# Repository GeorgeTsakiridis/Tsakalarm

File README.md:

# Tsakalarm
Tsakalarm is an open source project which includes the construction of a bedside table alarm clock, the software it runs as well as an Android app for easily configuring it

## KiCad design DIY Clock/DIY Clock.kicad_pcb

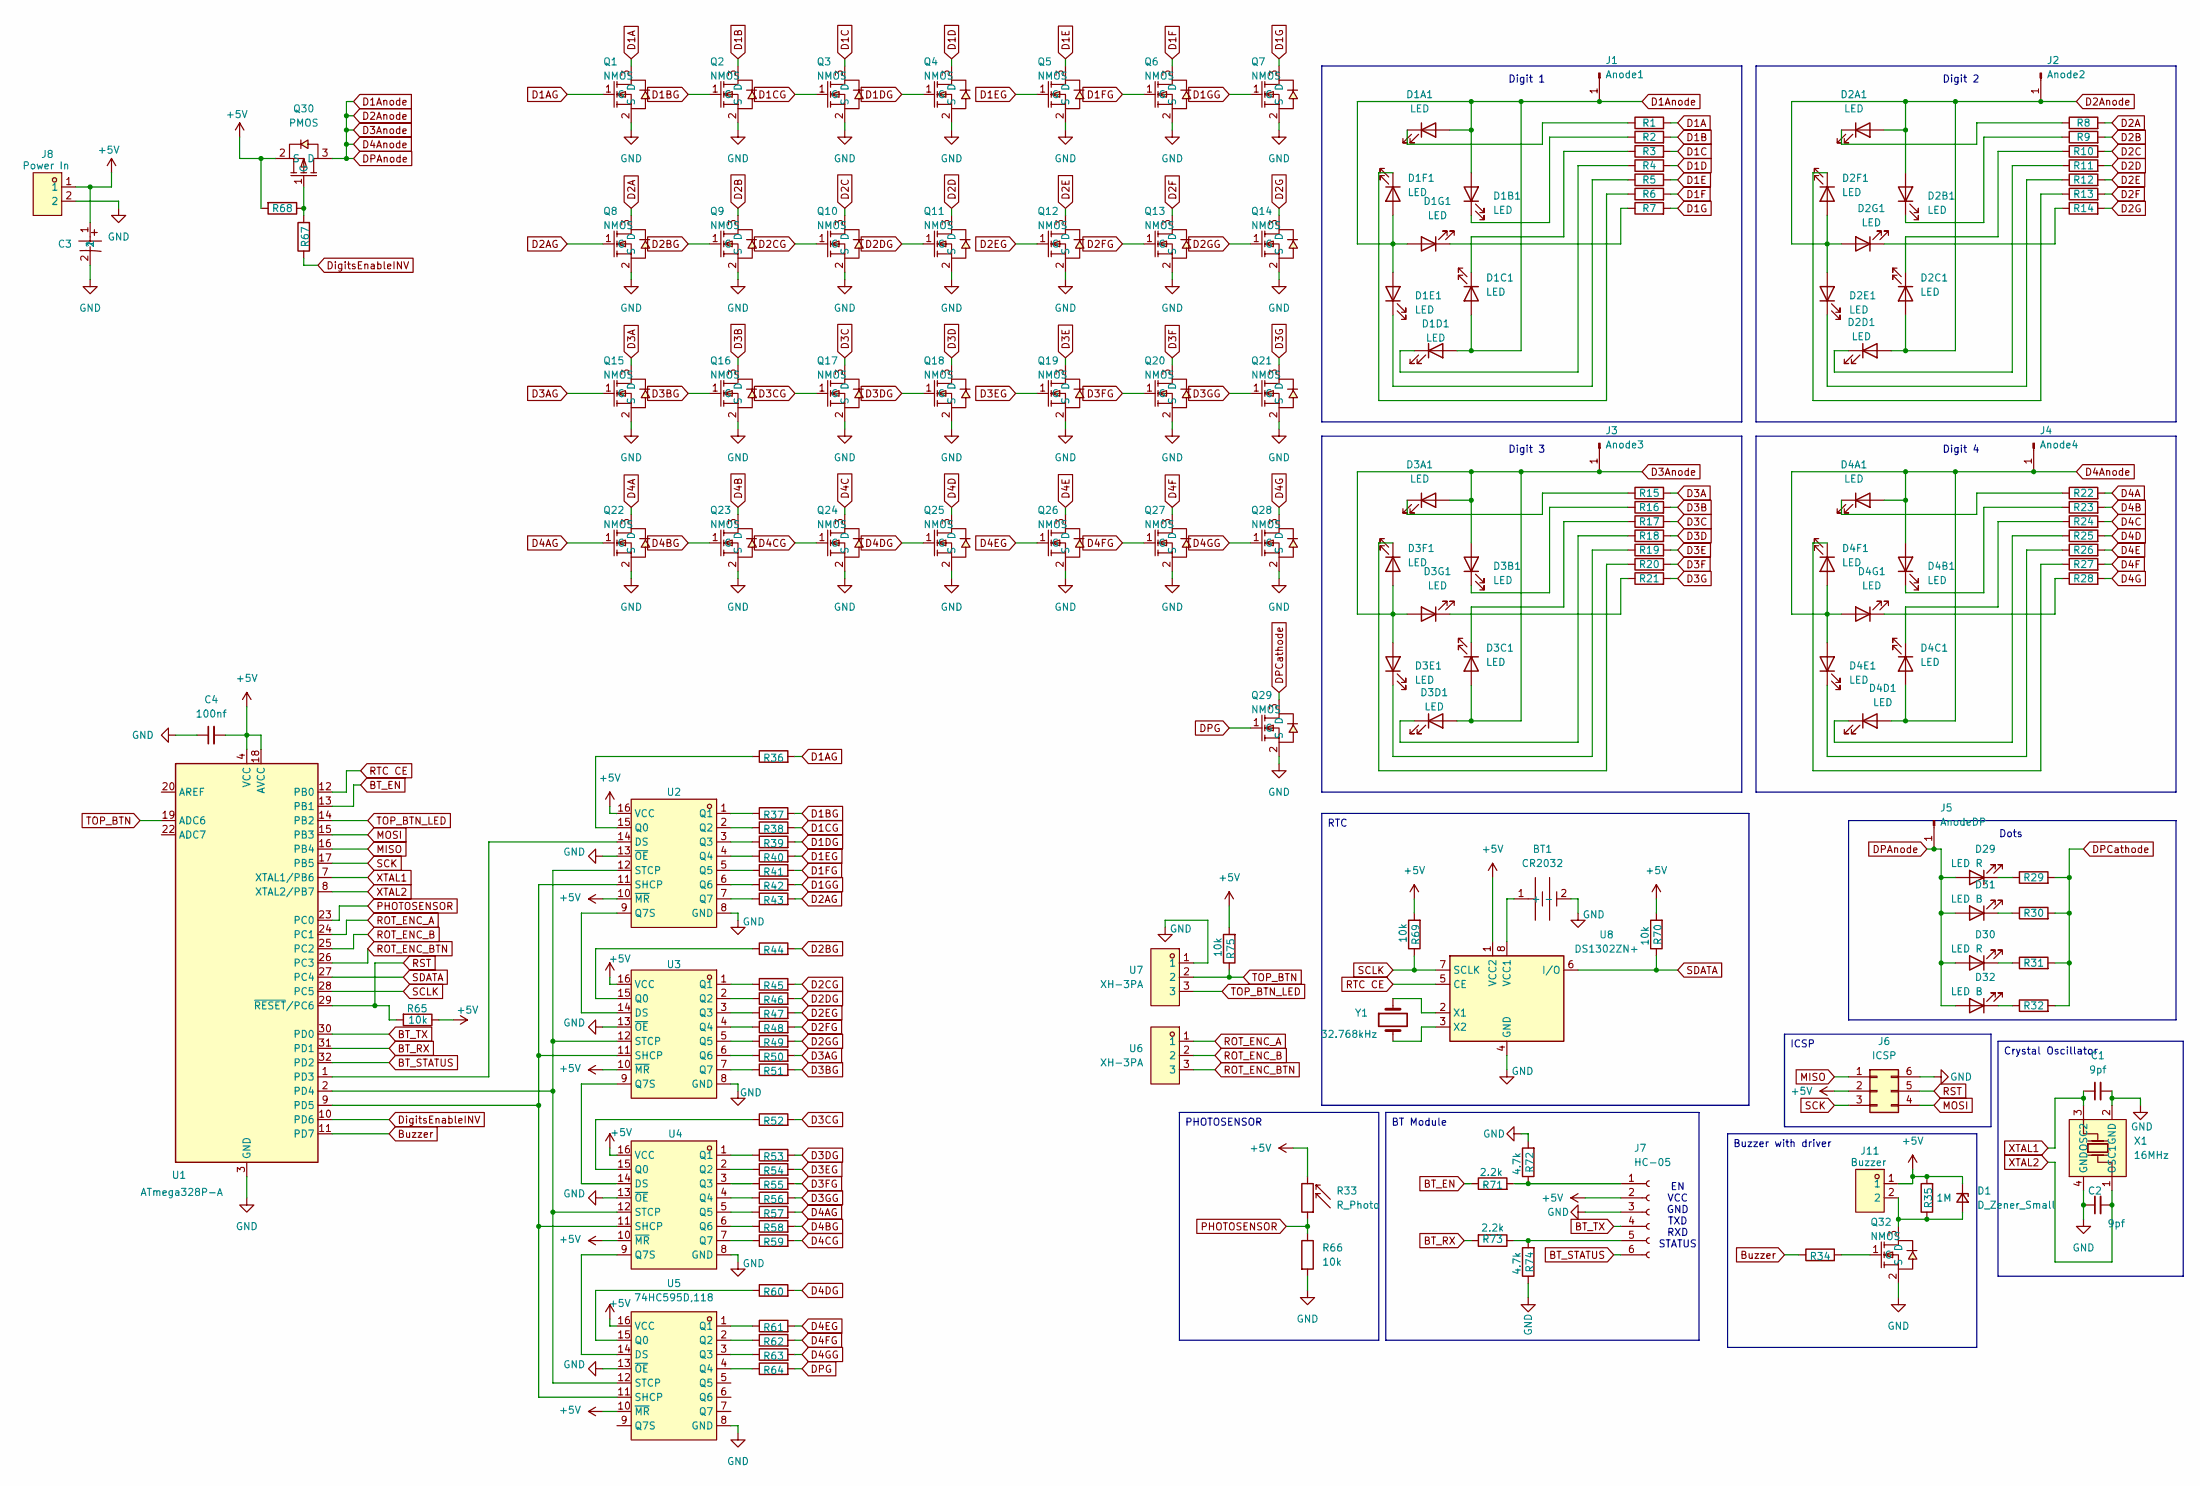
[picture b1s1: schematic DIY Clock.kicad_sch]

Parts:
BT1: CR2032; BAT-TH_120591-1; LCSC Part C575181
C1, C2: 9pf; C_0805_2012Metric_Pad1.18x1.45mm_HandSolder
C3: 35PX1000MEFC10X20; CAP-TH_BD10.0-P5.00-D1.0-FD; LCSC Part C136014
C4: 100nf; C_0805_2012Metric_Pad1.18x1.45mm_HandSolder
D1: D_Zener_Small; LL-34_L3.5-W1.5-RD
D1A1, D1B1, D1C1, D1D1, D1E1, D1F1, D1G1, D2A1, D2B1, D2C1, D2D1, D2E1, D2F1, D2G1, D3A1, D3B1, D3C1, D3D1, D3E1, D3F1, D3G1, D4A1, D4B1, D4C1, D4D1, D4E1, D4F1, D4G1: LED; PinHeader_1x01_P2.54mm_Vertical
D29, D30: LED R; PinHeader_1x01_P2.54mm_Vertical
D31, D32: LED B; PinHeader_1x01_P2.54mm_Vertical
J1: Anode1; PinHeader_1x01_P2.54mm_Vertical
J2: Anode2; PinHeader_1x01_P2.54mm_Vertical
J3: Anode3; PinHeader_1x01_P2.54mm_Vertical
J4: Anode4; PinHeader_1x01_P2.54mm_Vertical
J5: AnodeDP; PinHeader_1x01_P2.54mm_Vertical
J6: ICSP; PinHeader_2x03_P2.54mm_Vertical
J7: HC-05; PinHeader_1x06_P2.54mm_Vertical
J8: Power In; CONN-TH_XH-2A; LCSC Part C5258883
J11: Buzzer; PinHeader_1x02_P2.54mm_Vertical; LCSC Part C5258883
Q1, Q2, Q3, Q4, Q5, Q6, Q7, Q8, Q9, Q10, Q11, Q12, Q13, Q14, Q15, Q16, Q17, Q18, Q19, Q20, Q21, Q22, Q23, Q24, Q25, Q26, Q27, Q28, Q29, Q32: NMOS; SOT-23-3_L2.9-W1.3-P1.90-LS2.4-BR; LCSC Part C347475
Q30: PMOS; SOT-23_L2.9-W1.3-P1.90-LS2.4-BR; LCSC Part C347476
R1, R2, R3, R4, R5, R6, R7, R8, R9, R10, R11, R12, R13, R14, R15, R16, R17, R18, R19, R20, R21, R22, R23, R24, R25, R26, R27, R28, R29, R30, R31, R32: R; R_0805_2012Metric_Pad1.20x1.40mm_HandSolder
R33: R_Photo; PinHeader_1x02_P2.54mm_Vertical
R34, R36, R37, R38, R39, R40, R41, R42, R43, R44, R45, R46, R47, R48, R49, R50, R51, R52, R53, R54, R55, R56, R57, R58, R59, R60, R61, R62, R63, R64, R67: 1k; R_0805_2012Metric_Pad1.20x1.40mm_HandSolder
R35: 1M; R_0805_2012Metric_Pad1.20x1.40mm_HandSolder
R65, R66, R68, R69, R70, R75: 10k; R_0805_2012Metric_Pad1.20x1.40mm_HandSolder
R71, R73: 2.2k; R_0805_2012Metric_Pad1.20x1.40mm_HandSolder
R72, R74: 4.7k; R_0805_2012Metric_Pad1.20x1.40mm_HandSolder
U1: ATmega328P-A; TQFP-32_7x7mm_P0.8mm
U2, U3, U4, U5: 74HC595D,118; SOIC-16_L9.9-W3.9-P1.27-LS6.0-BL; LCSC Part C5947
U6, U7: XH-3PA; CONN-TH_3P-P2.50_ZHOURI_XH-3PA; LCSC Part C5258884
U8: DS1302ZN+; SOIC-8_3.9x4.9mm_P1.27mm
X1: 16MHz; CRYSTAL-SMD_4P-L3.2-W2.5-BL; LCSC Part C390767
Y1: 32.768kHz; Crystal_DS26_D2.0mm_L6.0mm_Horizontal

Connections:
+5V: C3.1, C4.2, D1.1 (K), J6.2, J7.2, J8.1, J11.1, Q30.2 (S), R33.2, R35.2, R65.1, R68.2, R69.2, R70.2, R75.2, U1.4 (VCC), U1.6 (VCC), U1.18 (AVCC), U2.10 (~MR), U2.16 (VCC), U3.10 (~MR), U3.16 (VCC), U4.10 (~MR), U4.16 (VCC), U5.10 (~MR), U5.16 (VCC), U8.1 (VCC2)
BT_EN: R71.1, U1.13 (PB1)
BT_RX: R73.2, U1.31 (PD1)
BT_STATUS: J7.6, U1.32 (PD2)
BT_TX: J7.4, U1.30 (PD0)
Buzzer: R34.1, U1.11 (PD7)
D1A: Q1.3 (D), R1.2
D1AG: Q1.1 (G), R36.2
D1Anode: D1A1.2 (A), D1B1.2 (A), D1C1.2 (A), D1D1.2 (A), D1E1.2 (A), D1F1.2 (A), D1G1.2 (A), D2A1.2 (A), D2B1.2 (A), D2C1.2 (A), D2D1.2 (A), D2E1.2 (A), D2F1.2 (A), D2G1.2 (A), D3A1.2 (A), D3B1.2 (A), D3C1.2 (A), D3D1.2 (A), D3E1.2 (A), D3F1.2 (A), D3G1.2 (A), D4A1.2 (A), D4B1.2 (A), D4C1.2 (A), D4D1.2 (A), D4E1.2 (A), D4F1.2 (A), D4G1.2 (A), D29.2 (A), D30.2 (A), D31.2 (A), D32.2 (A), J1.1, J2.1, J3.1, J4.1, J5.1, Q30.3 (D)
D1B: Q2.3 (D), R2.2
D1BG: Q2.1 (G), R37.2
D1C: Q3.3 (D), R3.2
D1CG: Q3.1 (G), R38.2
D1D: Q4.3 (D), R4.2
D1DG: Q4.1 (G), R39.2
D1E: Q5.3 (D), R5.2
D1EG: Q5.1 (G), R40.2
D1F: Q6.3 (D), R6.2
D1FG: Q6.1 (G), R41.2
D1G: Q7.3 (D), R7.2
D1GG: Q7.1 (G), R42.2
D2A: Q8.3 (D), R8.2
D2AG: Q8.1 (G), R43.2
D2B: Q9.3 (D), R9.2
D2BG: Q9.1 (G), R44.2
D2C: Q10.3 (D), R10.2
D2CG: Q10.1 (G), R45.2
D2D: Q11.3 (D), R11.2
D2DG: Q11.1 (G), R46.2
D2E: Q12.3 (D), R12.2
D2EG: Q12.1 (G), R47.2
D2F: Q13.3 (D), R13.2
D2FG: Q13.1 (G), R48.2
D2G: Q14.3 (D), R14.2
D2GG: Q14.1 (G), R49.2
D3A: Q15.3 (D), R15.2
D3AG: Q15.1 (G), R50.2
D3B: Q16.3 (D), R16.2
D3BG: Q16.1 (G), R51.2
D3C: Q17.3 (D), R17.2
D3CG: Q17.1 (G), R52.2
D3D: Q18.3 (D), R18.2
D3DG: Q18.1 (G), R53.2
D3E: Q19.3 (D), R19.2
D3EG: Q19.1 (G), R54.2
D3F: Q20.3 (D), R20.2
D3FG: Q20.1 (G), R55.2
D3G: Q21.3 (D), R21.2
D3GG: Q21.1 (G), R56.2
D4A: Q22.3 (D), R22.2
D4AG: Q22.1 (G), R57.2
D4B: Q23.3 (D), R23.2
D4BG: Q23.1 (G), R58.2
D4C: Q24.3 (D), R24.2
D4CG: Q24.1 (G), R59.2
D4D: Q25.3 (D), R25.2
D4DG: Q25.1 (G), R60.2
D4E: Q26.3 (D), R26.2
D4EG: Q26.1 (G), R61.2
D4F: Q27.3 (D), R27.2
D4FG: Q27.1 (G), R62.2
D4G: Q28.3 (D), R28.2
D4GG: Q28.1 (G), R63.2
DPCathode: Q29.3 (D), R29.2, R30.2, R31.2, R32.2
DPG: Q29.1 (G), R64.2
DigitsEnableINV: R67.1, U1.10 (PD6)
GND: BT1.2 (-), C1.2, C2.1, C3.2, C4.1, J6.6, J7.3, J8.2, Q1.2 (S), Q2.2 (S), Q3.2 (S), Q4.2 (S), Q5.2 (S), Q6.2 (S), Q7.2 (S), Q8.2 (S), Q9.2 (S), Q10.2 (S), Q11.2 (S), Q12.2 (S), Q13.2 (S), Q14.2 (S), Q15.2 (S), Q16.2 (S), Q17.2 (S), Q18.2 (S), Q19.2 (S), Q20.2 (S), Q21.2 (S), Q22.2 (S), Q23.2 (S), Q24.2 (S), Q25.2 (S), Q26.2 (S), Q27.2 (S), Q28.2 (S), Q29.2 (S), Q32.2 (S), R66.2, R72.2, R74.1, U1.3 (GND), U1.5 (GND), U1.21 (GND), U2.8 (GND), U2.13 (~OE), U3.8 (GND), U3.13 (~OE), U4.8 (GND), U4.13 (~OE), U5.8 (GND), U5.13 (~OE), U7.1, U8.4 (GND), X1.2 (GND), X1.4 (GND)
MISO: J6.1, U1.16 (PB4)
MOSI: J6.4, U1.15 (PB3)
unnamed: BT1.1 (+), U8.8 (VCC1)
unnamed: D1.2 (A), J11.2, Q32.3 (D), R35.1
unnamed: D1A1.1 (K), R1.1
unnamed: D1B1.1 (K), R2.1
unnamed: D1C1.1 (K), R3.1
unnamed: D1D1.1 (K), R4.1
unnamed: D1E1.1 (K), R5.1
unnamed: D1F1.1 (K), R6.1
unnamed: D1G1.1 (K), R7.1
unnamed: D2A1.1 (K), R8.1
unnamed: D2B1.1 (K), R9.1
unnamed: D2C1.1 (K), R10.1
unnamed: D2D1.1 (K), R11.1
unnamed: D2E1.1 (K), R12.1
unnamed: D2F1.1 (K), R13.1
unnamed: D2G1.1 (K), R14.1
unnamed: D3A1.1 (K), R15.1
unnamed: D3B1.1 (K), R16.1
unnamed: D3C1.1 (K), R17.1
unnamed: D3D1.1 (K), R18.1
unnamed: D3E1.1 (K), R19.1
unnamed: D3F1.1 (K), R20.1
unnamed: D3G1.1 (K), R21.1
unnamed: D4A1.1 (K), R22.1
unnamed: D4B1.1 (K), R23.1
unnamed: D4C1.1 (K), R24.1
unnamed: D4D1.1 (K), R25.1
unnamed: D4E1.1 (K), R26.1
unnamed: D4F1.1 (K), R27.1
unnamed: D4G1.1 (K), R28.1
unnamed: D29.1 (K), R29.1
unnamed: D30.1 (K), R31.1
unnamed: D31.1 (K), R30.1
unnamed: D32.1 (K), R32.1
unnamed: J7.1, R71.2, R72.1
unnamed: J7.5, R73.1, R74.2
unnamed: Q30.1 (G), R67.2, R68.1
unnamed: Q32.1 (G), R34.2
unnamed: U1.1 (PD3), U2.14 (DS)
unnamed: U1.2 (PD4), U2.12 (STCP), U3.12 (STCP), U4.12 (STCP), U5.12 (STCP)
unnamed: U1.9 (PD5), U2.11 (SHCP), U3.11 (SHCP), U4.11 (SHCP), U5.11 (SHCP)
unnamed: R36.1, U2.15 (Q0)
unnamed: R37.1, U2.1 (Q1)
unnamed: R38.1, U2.2 (Q2)
unnamed: R39.1, U2.3 (Q3)
unnamed: R40.1, U2.4 (Q4)
unnamed: R41.1, U2.5 (Q5)
unnamed: R42.1, U2.6 (Q6)
unnamed: R43.1, U2.7 (Q7)
unnamed: U2.9 (Q7S), U3.14 (DS)
unnamed: R44.1, U3.15 (Q0)
unnamed: R45.1, U3.1 (Q1)
unnamed: R46.1, U3.2 (Q2)
unnamed: R47.1, U3.3 (Q3)
unnamed: R48.1, U3.4 (Q4)
unnamed: R49.1, U3.5 (Q5)
unnamed: R50.1, U3.6 (Q6)
unnamed: R51.1, U3.7 (Q7)
unnamed: U3.9 (Q7S), U4.14 (DS)
unnamed: R52.1, U4.15 (Q0)
unnamed: R53.1, U4.1 (Q1)
unnamed: R54.1, U4.2 (Q2)
unnamed: R55.1, U4.3 (Q3)
unnamed: R56.1, U4.4 (Q4)
unnamed: R57.1, U4.5 (Q5)
unnamed: R58.1, U4.6 (Q6)
unnamed: R59.1, U4.7 (Q7)
unnamed: U4.9 (Q7S), U5.14 (DS)
unnamed: R60.1, U5.15 (Q0)
unnamed: R61.1, U5.1 (Q1)
unnamed: R62.1, U5.2 (Q2)
unnamed: R63.1, U5.3 (Q3)
unnamed: R64.1, U5.4 (Q4)
unnamed: U8.2 (X1), Y1.1
unnamed: U8.3 (X2), Y1.2
PHOTOSENSOR: R33.1, R66.1, U1.23 (PC0)
ROT_ENC_A: U1.24 (PC1), U6.1
ROT_ENC_B: U1.25 (PC2), U6.2
ROT_ENC_BTN: U1.26 (PC3), U6.3
RST: J6.5, R65.2, U1.29 (~RESET/PC6)
RTC CE: U1.12 (PB0), U8.5 (CE)
SCK: J6.3, U1.17 (PB5)
SCLK: R69.1, U1.28 (PC5), U8.7 (SCLK)
SDATA: R70.1, U1.27 (PC4), U8.6 (I/O)
TOP_BTN: R75.1, U1.19 (ADC6), U7.2
TOP_BTN_LED: U1.14 (PB2), U7.3
XTAL1: C1.1, U1.7 (XTAL1/PB6), X1.3 (OSC2)
XTAL2: C2.2, U1.8 (XTAL2/PB7), X1.1 (OSC1)

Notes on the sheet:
EN VCC GND TXD RXD STATUS
Dots
Digit 1
Digit 3
Digit 4
Digit 2
RTC
ICSP
BT Module
Crystal Oscillator
Buzzer with driver
PHOTOSENSOR

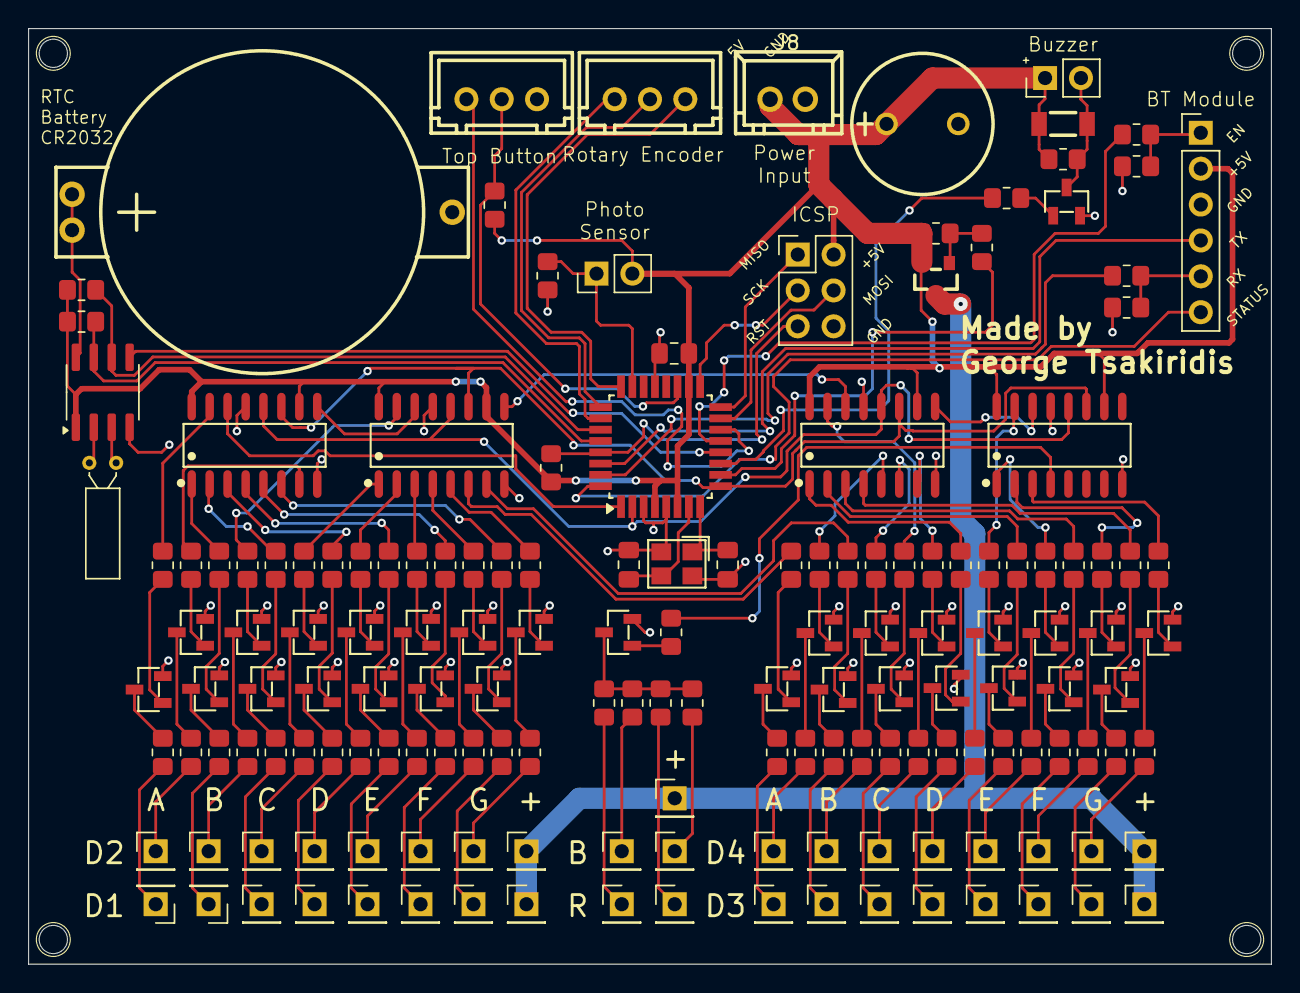
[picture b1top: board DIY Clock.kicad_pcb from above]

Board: 2 copper layers, 88.0 x 66.2 mm, 163 parts (0 on the bottom side), 157 nets.

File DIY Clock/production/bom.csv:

Designator,Footprint,Quantity,Value,LCSC Part #
BT1,BAT-TH_120591-1,1,CR2032,C575181
"C1, C2",0805,2,9pf,
C3,CAP-TH_BD10.0-P5.00-D1.0-FD,1,35PX1000MEFC10X20,C136014
C4,0805,1,100nf,
D1,LL-34_L3.5-W1.5-RD,1,D_Zener_Small,
"D1A1, D1B1, D1C1, D1D1, D1E1, D1F1, D1G1, D2A1, D2B1, D2C1, D2D1, D2E1, D2F1, D2G1, D3A1, D3B1, D3C1, D3D1, D3E1, D3F1, D3G1, D4A1, D4B1, D4C1, D4D1, D4E1, D4F1, D4G1",PinHeader_1x01_P2.54mm_Vertical,28,LED,
"D29, D30",PinHeader_1x01_P2.54mm_Vertical,2,LED R,
"D31, D32",PinHeader_1x01_P2.54mm_Vertical,2,LED B,
J1,PinHeader_1x01_P2.54mm_Vertical,1,Anode1,
J10,PinHeader_1x03_P2.54mm_Vertical,1,Digits Power Converter,C5258884
J11,PinHeader_1x02_P2.54mm_Vertical,1,Buzzer,C5258883
J2,PinHeader_1x01_P2.54mm_Vertical,1,Anode2,
J3,PinHeader_1x01_P2.54mm_Vertical,1,Anode3,
J4,PinHeader_1x01_P2.54mm_Vertical,1,Anode4,
J5,PinHeader_1x01_P2.54mm_Vertical,1,AnodeDP,
J6,PinHeader_2x03_P2.54mm_Vertical,1,ICSP,
J7,PinHeader_1x06_P2.54mm_Vertical,1,HC-05,
J8,PinHeader_1x02_P2.54mm_Vertical,1,Power In,C5258883
J9,PinHeader_1x03_P2.54mm_Vertical,1,5V Converter,C5258884
"Q1, Q10, Q11, Q12, Q13, Q14, Q15, Q16, Q17, Q18, Q19, Q2, Q20, Q21, Q22, Q23, Q24, Q25, Q26, Q27, Q28, Q29, Q3, Q32, Q4, Q5, Q6, Q7, Q8, Q9",SOT-23-3_L2.9-W1.3-P1.90-LS2.4-BR,30,NMOS,C347475
Q30,SOT-23_L2.9-W1.3-P1.90-LS2.4-BR,1,PMOS,C347476
"R1, R10, R11, R12, R13, R14, R15, R16, R17, R18, R19, R2, R20, R21, R22, R23, R24, R25, R26, R27, R28, R29, R3, R30, R31, R32, R4, R5, R6, R7, R8, R9",0805,32,R,
R33,PinHeader_1x02_P2.54mm_Vertical,1,R_Photo,
"R34, R36, R37, R38, R39, R40, R41, R42, R43, R44, R45, R46, R47, R48, R49, R50, R51, R52, R53, R54, R55, R56, R57, R58, R59, R60, R61, R62, R63, R64, R67",0805,31,1k,
R35,0805,1,1M,
"R65, R66, R68, R69, R70",0805,5,10k,
"R71, R73",0805,2,2.2k,
"R72, R74",0805,2,4.7k,
U1,TQFP-32_7x7mm_P0.8mm,1,ATmega328P-A,
"U2, U3, U4, U5",SOIC-16_L9.9-W3.9-P1.27-LS6.0-BL,4,"74HC595D,118",C5947
U8,SOIC-8_3.9x4.9mm_P1.27mm,1,DS1302ZN+,
X1,CRYSTAL-SMD_4P-L3.2-W2.5-BL,1,16MHz,C390767
Y1,Crystal_DS26_D2.0mm_L6.0mm_Horizontal,1,32.768kHz,

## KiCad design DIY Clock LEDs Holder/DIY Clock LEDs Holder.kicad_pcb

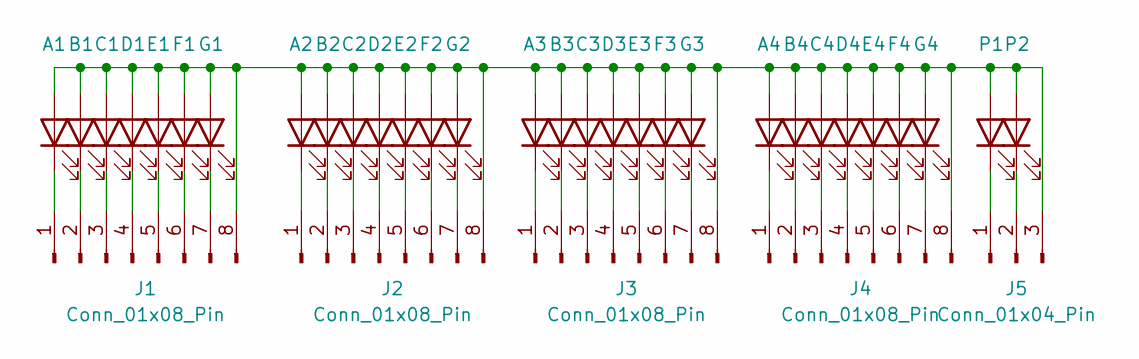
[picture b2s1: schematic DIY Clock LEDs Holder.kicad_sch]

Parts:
A1, A2, A3, A4: LED; LED Filament 12.3mm
B1, B2, B3, B4: LED; LED Filament 12.3mm
C1, C2, C3, C4: LED; LED Filament 12.3mm
D1, D2, D3, D4: LED; LED Filament 12.3mm
E1, E2, E3, E4: LED; LED Filament 12.3mm
F1, F2, F3, F4: LED; LED Filament 12.3mm
G1, G2, G3, G4: LED; LED Filament 12.3mm
J1, J2, J3, J4: Conn_01x08_Pin; PinHeader_1x08_P2.00mm_Vertical
J5: Conn_01x04_Pin; PinHeader_1x03_P2.00mm_Vertical
P1, P2: LED; LED Filament 12.3mm

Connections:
unnamed: A1.2 (A), A2.2 (A), A3.2 (A), A4.2 (A), B1.2 (A), B2.2 (A), B3.2 (A), B4.2 (A), C1.2 (A), C2.2 (A), C3.2 (A), C4.2 (A), D1.2 (A), D2.2 (A), D3.2 (A), D4.2 (A), E1.2 (A), E2.2 (A), E3.2 (A), E4.2 (A), F1.2 (A), F2.2 (A), F3.2 (A), F4.2 (A), G1.2 (A), G2.2 (A), G3.2 (A), G4.2 (A), J1.8, J2.8, J3.8, J4.8, J5.3, P1.2 (A), P2.2 (A)
unnamed: A1.1 (K), J1.1
unnamed: A2.1 (K), J2.1
unnamed: A3.1 (K), J3.1
unnamed: A4.1 (K), J4.1
unnamed: B1.1 (K), J1.2
unnamed: B2.1 (K), J2.2
unnamed: B3.1 (K), J3.2
unnamed: B4.1 (K), J4.2
unnamed: C1.1 (K), J1.3
unnamed: C2.1 (K), J2.3
unnamed: C3.1 (K), J3.3
unnamed: C4.1 (K), J4.3
unnamed: D1.1 (K), J1.4
unnamed: D2.1 (K), J2.4
unnamed: D3.1 (K), J3.4
unnamed: D4.1 (K), J4.4
unnamed: E1.1 (K), J1.5
unnamed: E2.1 (K), J2.5
unnamed: E3.1 (K), J3.5
unnamed: E4.1 (K), J4.5
unnamed: F1.1 (K), J1.6
unnamed: F2.1 (K), J2.6
unnamed: F3.1 (K), J3.6
unnamed: F4.1 (K), J4.6
unnamed: G1.1 (K), J1.7
unnamed: G2.1 (K), J2.7
unnamed: G3.1 (K), J3.7
unnamed: G4.1 (K), J4.7
unnamed: J5.1, P1.1 (K)
unnamed: J5.2, P2.1 (K)

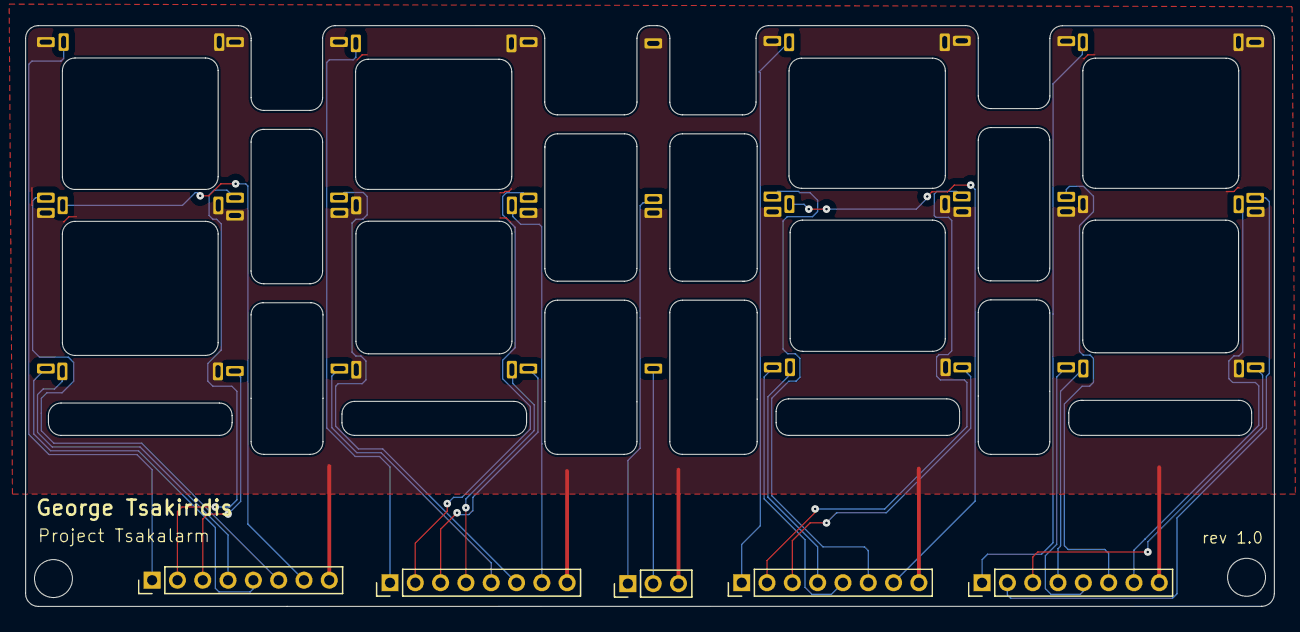
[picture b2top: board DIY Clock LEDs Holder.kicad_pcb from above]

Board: 2 copper layers, 98.7 x 45.9 mm, 35 parts (0 on the bottom side), 31 nets.

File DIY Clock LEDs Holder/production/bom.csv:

Designator,Footprint,Quantity,Value,LCSC Part #
"A1, A2, A3, A4, B1, B2, B3, B4, C1, C2, C3, C4, D1, D2, D3, D4, E1, E2, E3, E4, F1, F2, F3, F4, G1, G2, G3, G4, P1, P2",LED Filament 12.3mm,30,LED,
"J1, J2, J3, J4",PinHeader_1x08_P2.00mm_Vertical,4,Conn_01x08_Pin,
J5,PinHeader_1x03_P2.00mm_Vertical,1,Conn_01x04_Pin,

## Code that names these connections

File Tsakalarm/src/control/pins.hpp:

#ifndef alarm_pins_h
#define alarm_pins_h

#define BT_TX_PIN 0
#define BT_RX_PIN 1
#define BT_STATUS_PIN 2
#define BT_ENABLE_PIN 9

#define SR_DATA_PIN 3
#define SR_ST_CLK_PIN 4
#define SR_OUT_CLK_PIN 5
#define DIGITS_ENABLE_PIN 6

#define RTC_ENABLE_PIN 8
#define RTC_DATA_PIN 18
#define RTC_CLK_PIN 19

#define ROT_ENC_A A1
#define ROT_ENC_B A2
#define ROT_ENC_BTN A3

#define TOP_BTN A6
#define TOP_BTN_LED 10

#define BUZZER_PIN 7
#define PHOTORESISTOR_PIN A0

#endif
